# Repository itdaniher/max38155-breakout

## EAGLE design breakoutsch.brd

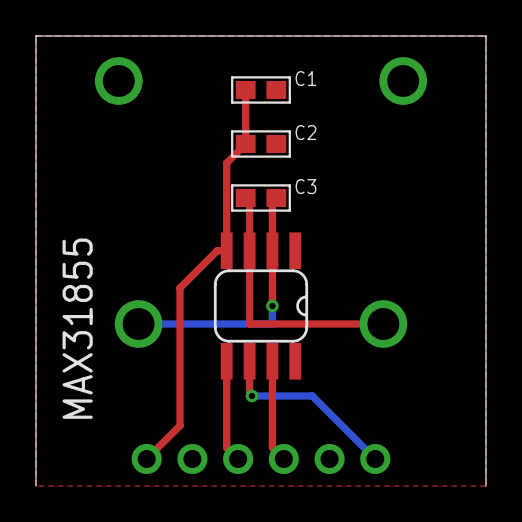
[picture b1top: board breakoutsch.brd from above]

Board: 2 copper layers, 25.0 x 25.0 mm, 6 parts (1 on the bottom side), 7 nets.

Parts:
C1: .1uF; 0603
C2: 1uF; 0603
C3: 10nF; 0603
JP1: 1X06_ROUND
U$1: MAX31855; SO-08
U$2: OMEGAPCC-SMP; PCC-SMP

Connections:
3V3: C1.1, C2.1, JP1.1, U$1.4
CS: JP1.6, U$1.6
GND: C1.2, C2.2, JP1.2, U$1.1, U$2.GND@1, U$2.GND@4
SCK: JP1.3, U$1.5
SO: JP1.4, U$1.7
T+: C3.1, U$1.3, U$2.+2
T-: C3.2, U$1.2, U$2.-3

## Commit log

2013-01-07 rename files so that they're sane
2013-05-31 chamfer, label, add resistor jumper for use with xmega breakout - design confirmed working.
